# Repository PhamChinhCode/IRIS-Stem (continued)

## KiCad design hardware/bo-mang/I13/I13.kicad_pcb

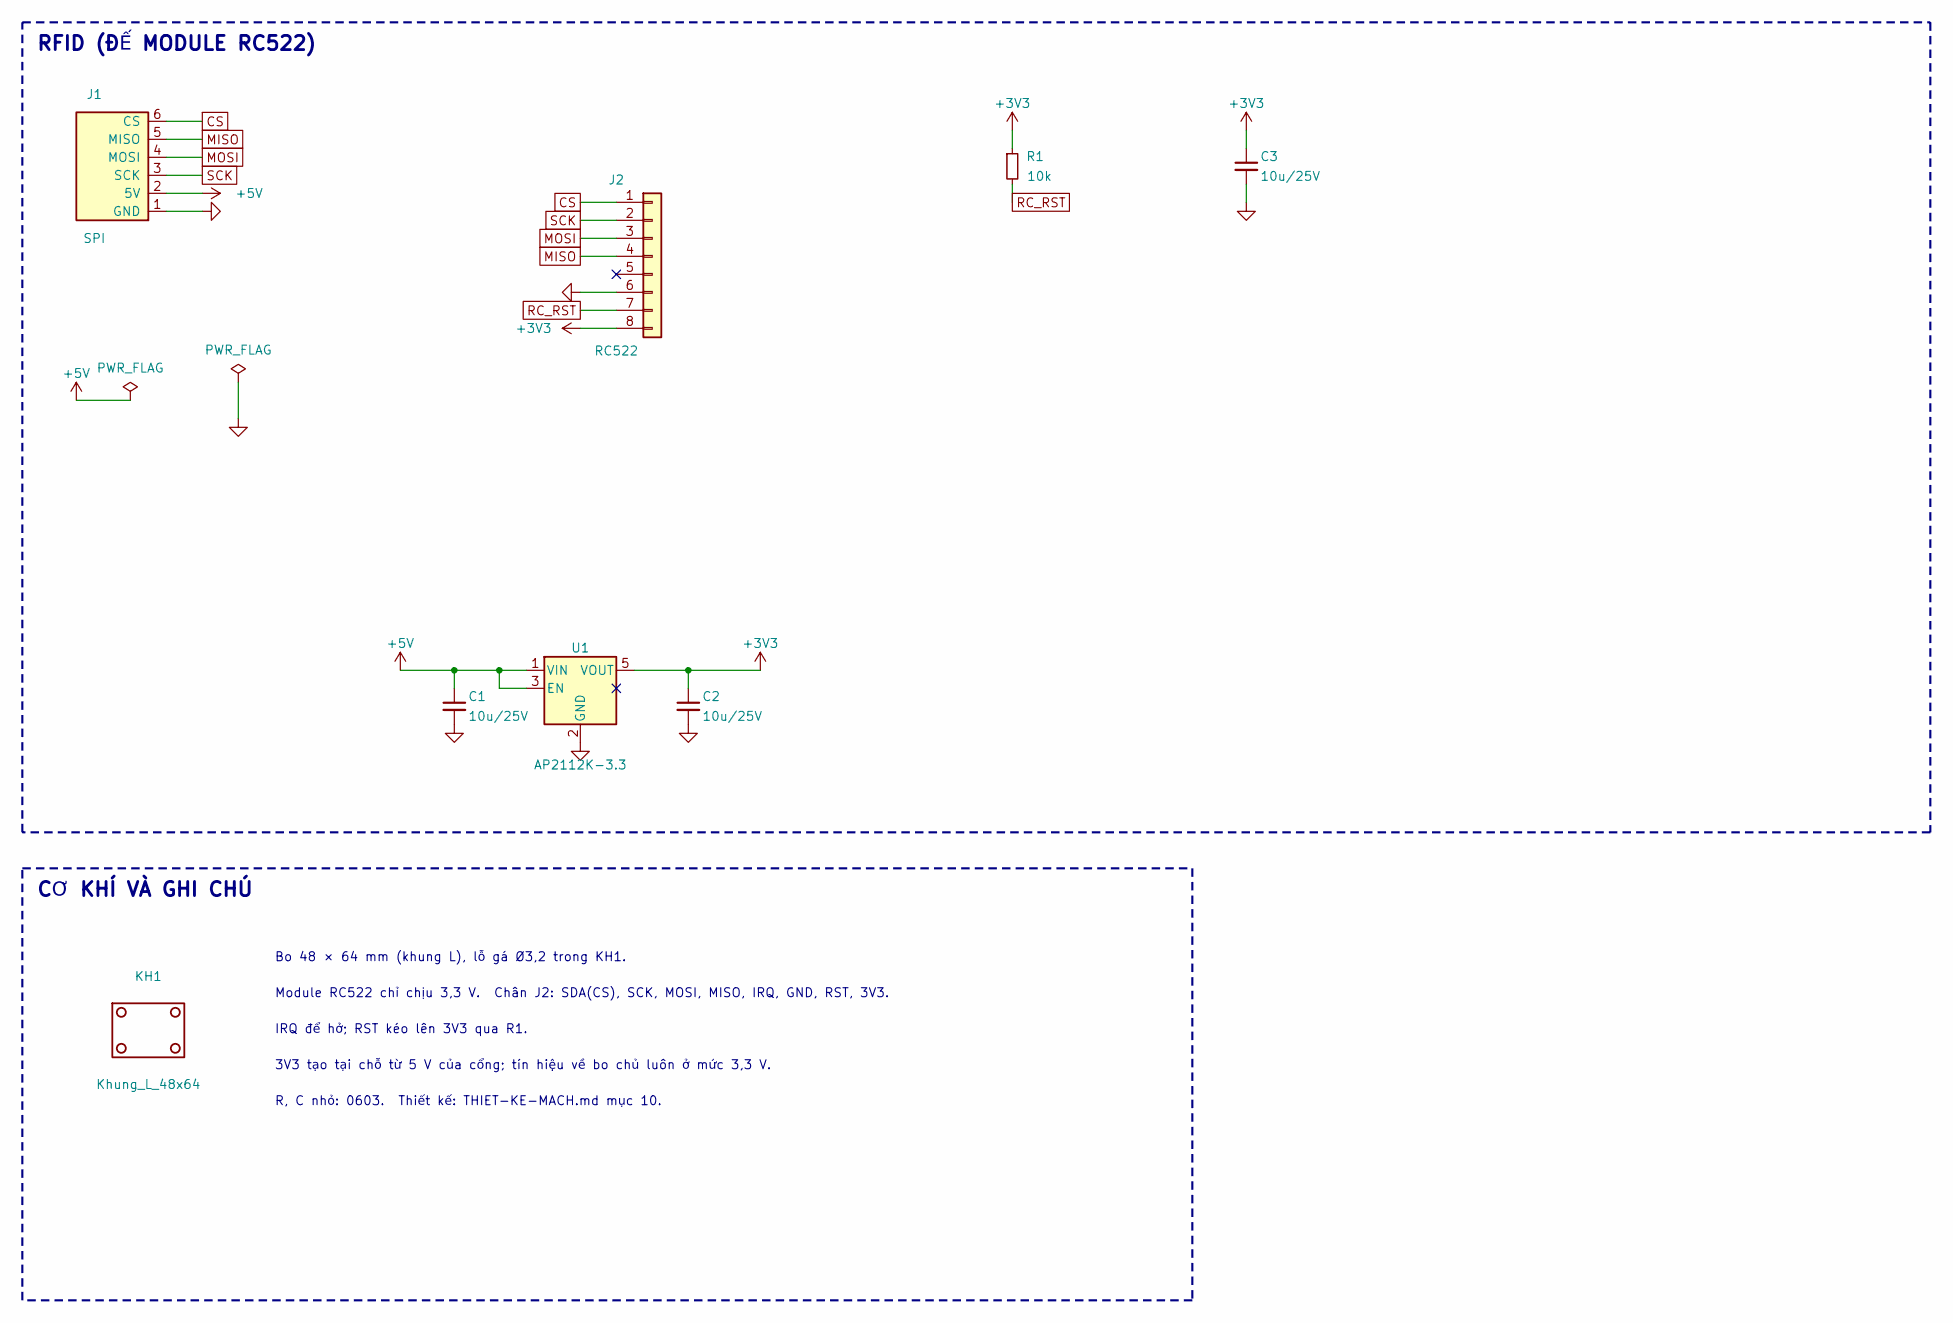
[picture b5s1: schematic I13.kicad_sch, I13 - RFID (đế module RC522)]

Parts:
C1, C2, C3: 10u/25V; C_0805_2012Metric
J1: SPI; Cong_PH_6P_Ngang
J2: RC522; PinSocket_1x08_P2.54mm_Vertical
KH1: Khung_L_48x64
R1: 10k; R_0603_1608Metric
U1: AP2112K-3.3; SOT-23-5; MPN AP2112K-3.3TRG1

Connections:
+3V3: C2.1, C3.1, J2.8, R1.1, U1.5 (VOUT)
+5V: C1.1, J1.2 (5V), U1.1 (VIN), U1.3 (EN)
CS: J1.6 (CS), J2.1
GND: C1.2, C2.2, C3.2, J1.1 (GND), J2.6, U1.2 (GND)
MISO: J1.5 (MISO), J2.4
MOSI: J1.4 (MOSI), J2.3
RC_RST: J2.7, R1.2
SCK: J1.3 (SCK), J2.2

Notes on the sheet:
RFID (ĐẾ MODULE RC522)
CƠ KHÍ VÀ GHI CHÚ
Bo 48 × 64 mm (khung L), lỗ gá Ø3,2 trong KH1.
Module RC522 chỉ chịu 3,3 V. Chân J2: SDA(CS), SCK, MOSI, MISO, IRQ, GND, RST, 3V3.
IRQ để hở; RST kéo lên 3V3 qua R1.
3V3 tạo tại chỗ từ 5 V của cổng; tín hiệu về bo chủ luôn ở mức 3,3 V.
R, C nhỏ: 0603. Thiết kế: THIET-KE-MACH.md mục 10.

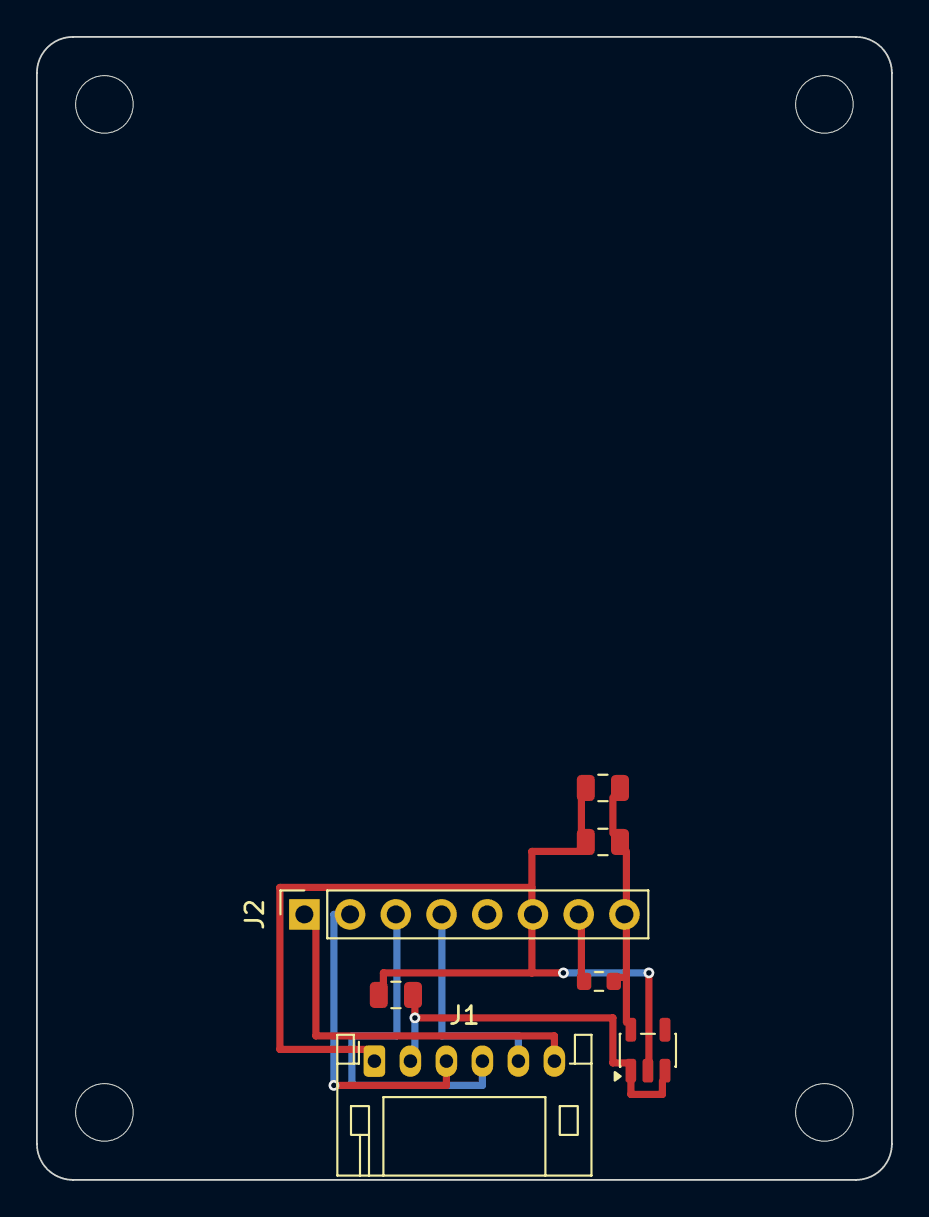
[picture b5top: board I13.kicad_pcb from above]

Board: 2 copper layers, 47.5 x 63.5 mm, 8 parts (0 on the bottom side), 8 nets.

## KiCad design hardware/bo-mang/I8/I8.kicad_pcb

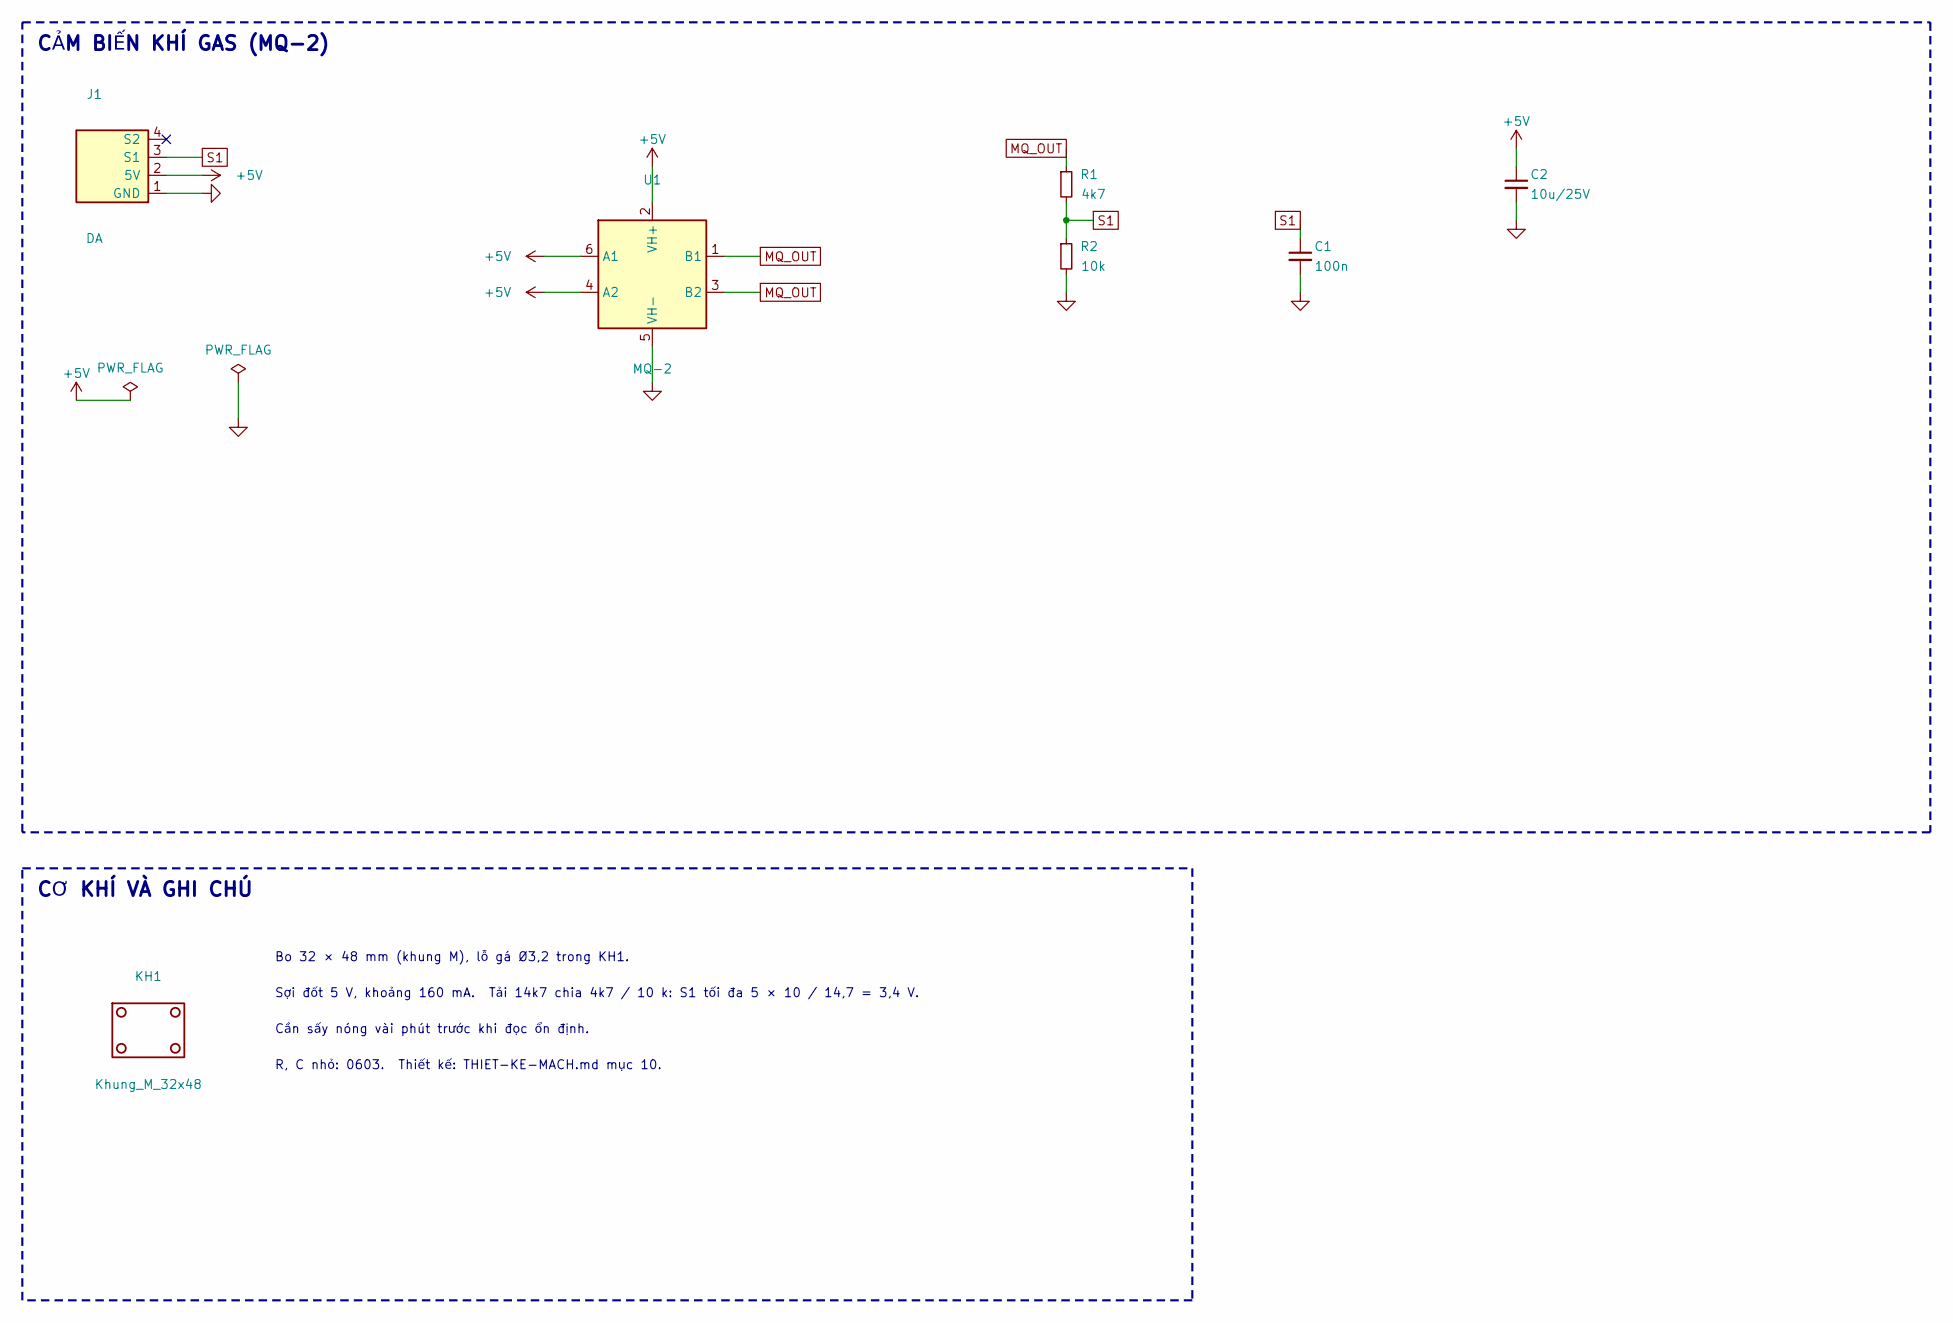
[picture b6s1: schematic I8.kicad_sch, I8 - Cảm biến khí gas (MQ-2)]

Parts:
C1: 100n; C_0603_1608Metric
C2: 10u/25V; C_0805_2012Metric
J1: DA; Cong_PH_4P_Ngang
KH1: Khung_M_32x48
R1: 4k7; R_0603_1608Metric
R2: 10k; R_0603_1608Metric
U1: MQ-2; MQ-6; MPN MQ-2

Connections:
+5V: C2.1, J1.2 (5V), U1.2 (VH+), U1.4 (A2), U1.6 (A1)
GND: C1.2, C2.2, J1.1 (GND), R2.2, U1.5 (VH-)
MQ_OUT: R1.1, U1.1 (B1), U1.3 (B2)
S1: C1.1, J1.3 (S1), R1.2, R2.1

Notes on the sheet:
CẢM BIẾN KHÍ GAS (MQ-2)
CƠ KHÍ VÀ GHI CHÚ
Bo 32 × 48 mm (khung M), lỗ gá Ø3,2 trong KH1.
Sợi đốt 5 V, khoảng 160 mA. Tải 14k7 chia 4k7 / 10 k: S1 tối đa 5 × 10 / 14,7 = 3,4 V.
Cần sấy nóng vài phút trước khi đọc ổn định.
R, C nhỏ: 0603. Thiết kế: THIET-KE-MACH.md mục 10.

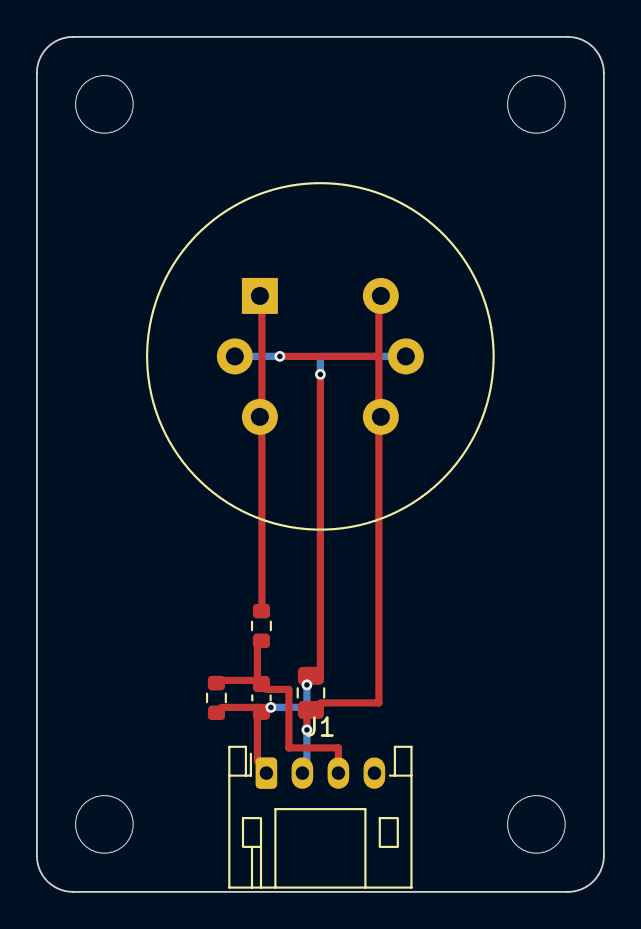
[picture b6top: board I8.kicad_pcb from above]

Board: 2 copper layers, 31.5 x 47.5 mm, 7 parts (0 on the bottom side), 4 nets.

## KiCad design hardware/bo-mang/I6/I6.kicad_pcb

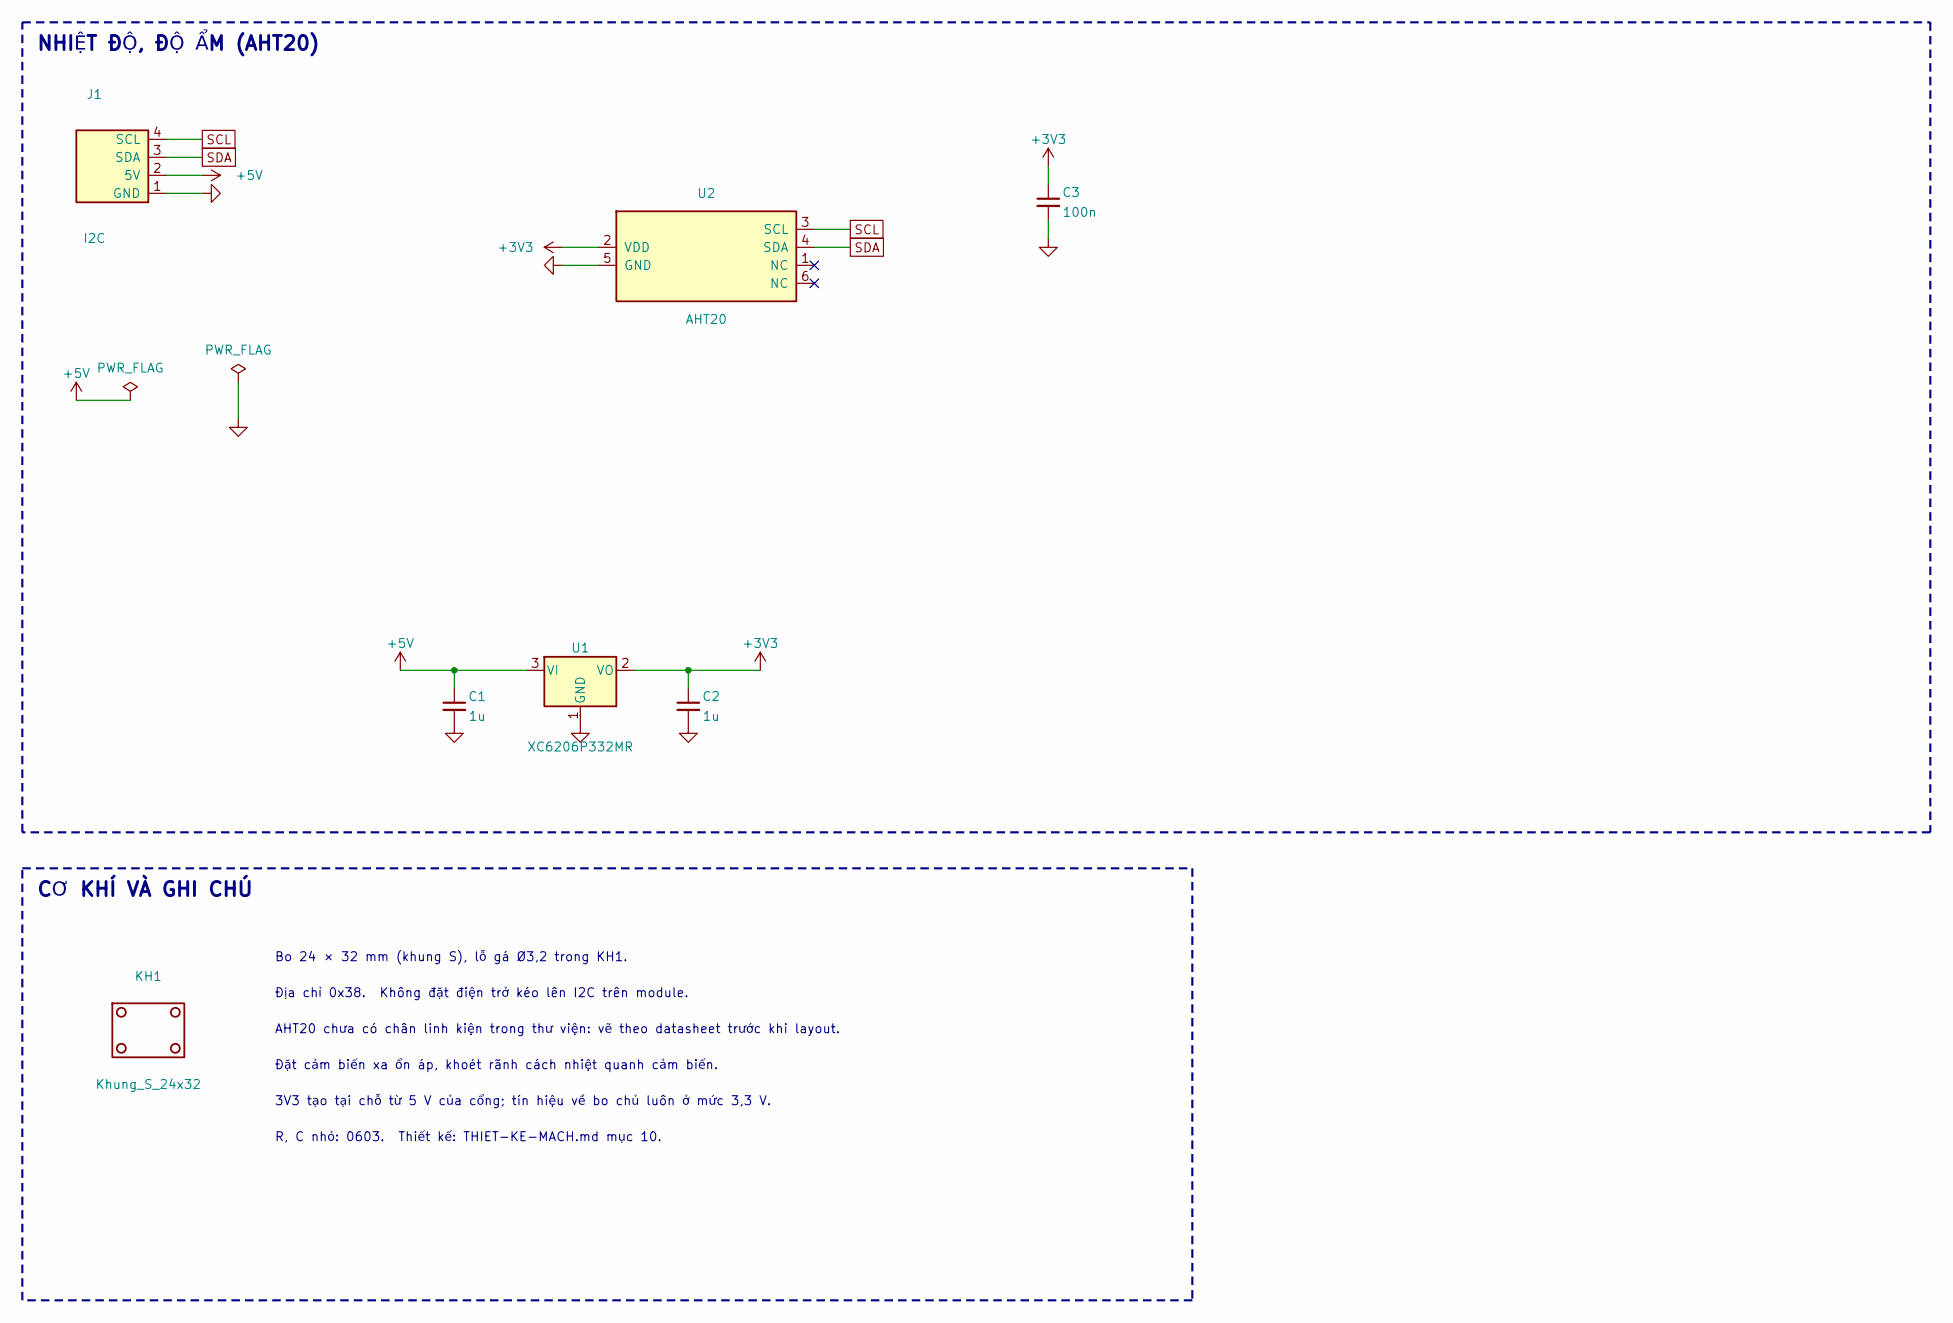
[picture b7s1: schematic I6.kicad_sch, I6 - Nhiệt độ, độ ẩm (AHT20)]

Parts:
C1, C2: 1u; C_0603_1608Metric
C3: 100n; C_0603_1608Metric
J1: I2C; Cong_PH_4P_Ngang
KH1: Khung_S_24x32
U1: XC6206P332MR; SOT-23-3; MPN XC6206P332MR
U2: AHT20; AHT20_DFN6_3x3; MPN AHT20

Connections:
+3V3: C2.1, C3.1, U1.2 (VO), U2.2 (VDD)
+5V: C1.1, J1.2 (5V), U1.3 (VI)
GND: C1.2, C2.2, C3.2, J1.1 (GND), U1.1 (GND), U2.5 (GND)
SCL: J1.4 (SCL), U2.3 (SCL)
SDA: J1.3 (SDA), U2.4 (SDA)

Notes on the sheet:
NHIỆT ĐỘ, ĐỘ ẨM (AHT20)
CƠ KHÍ VÀ GHI CHÚ
Bo 24 × 32 mm (khung S), lỗ gá Ø3,2 trong KH1.
Địa chỉ 0x38. Không đặt điện trở kéo lên I2C trên module.
AHT20 chưa có chân linh kiện trong thư viện: vẽ theo datasheet trước khi layout.
Đặt cảm biến xa ổn áp, khoét rãnh cách nhiệt quanh cảm biến.
3V3 tạo tại chỗ từ 5 V của cổng; tín hiệu về bo chủ luôn ở mức 3,3 V.
R, C nhỏ: 0603. Thiết kế: THIET-KE-MACH.md mục 10.

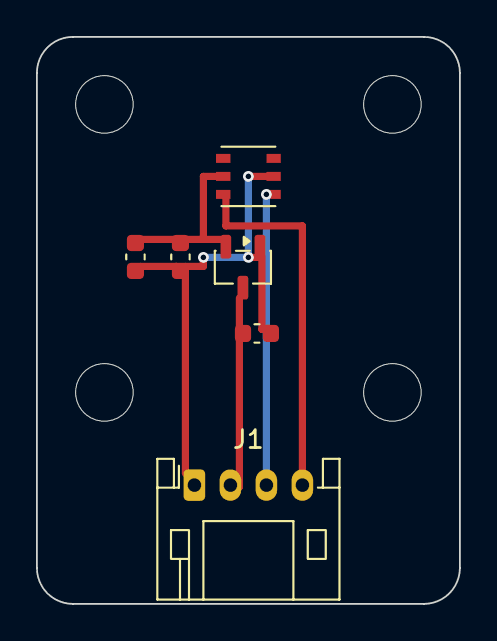
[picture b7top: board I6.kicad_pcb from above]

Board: 2 copper layers, 23.5 x 31.5 mm, 7 parts (0 on the bottom side), 5 nets.

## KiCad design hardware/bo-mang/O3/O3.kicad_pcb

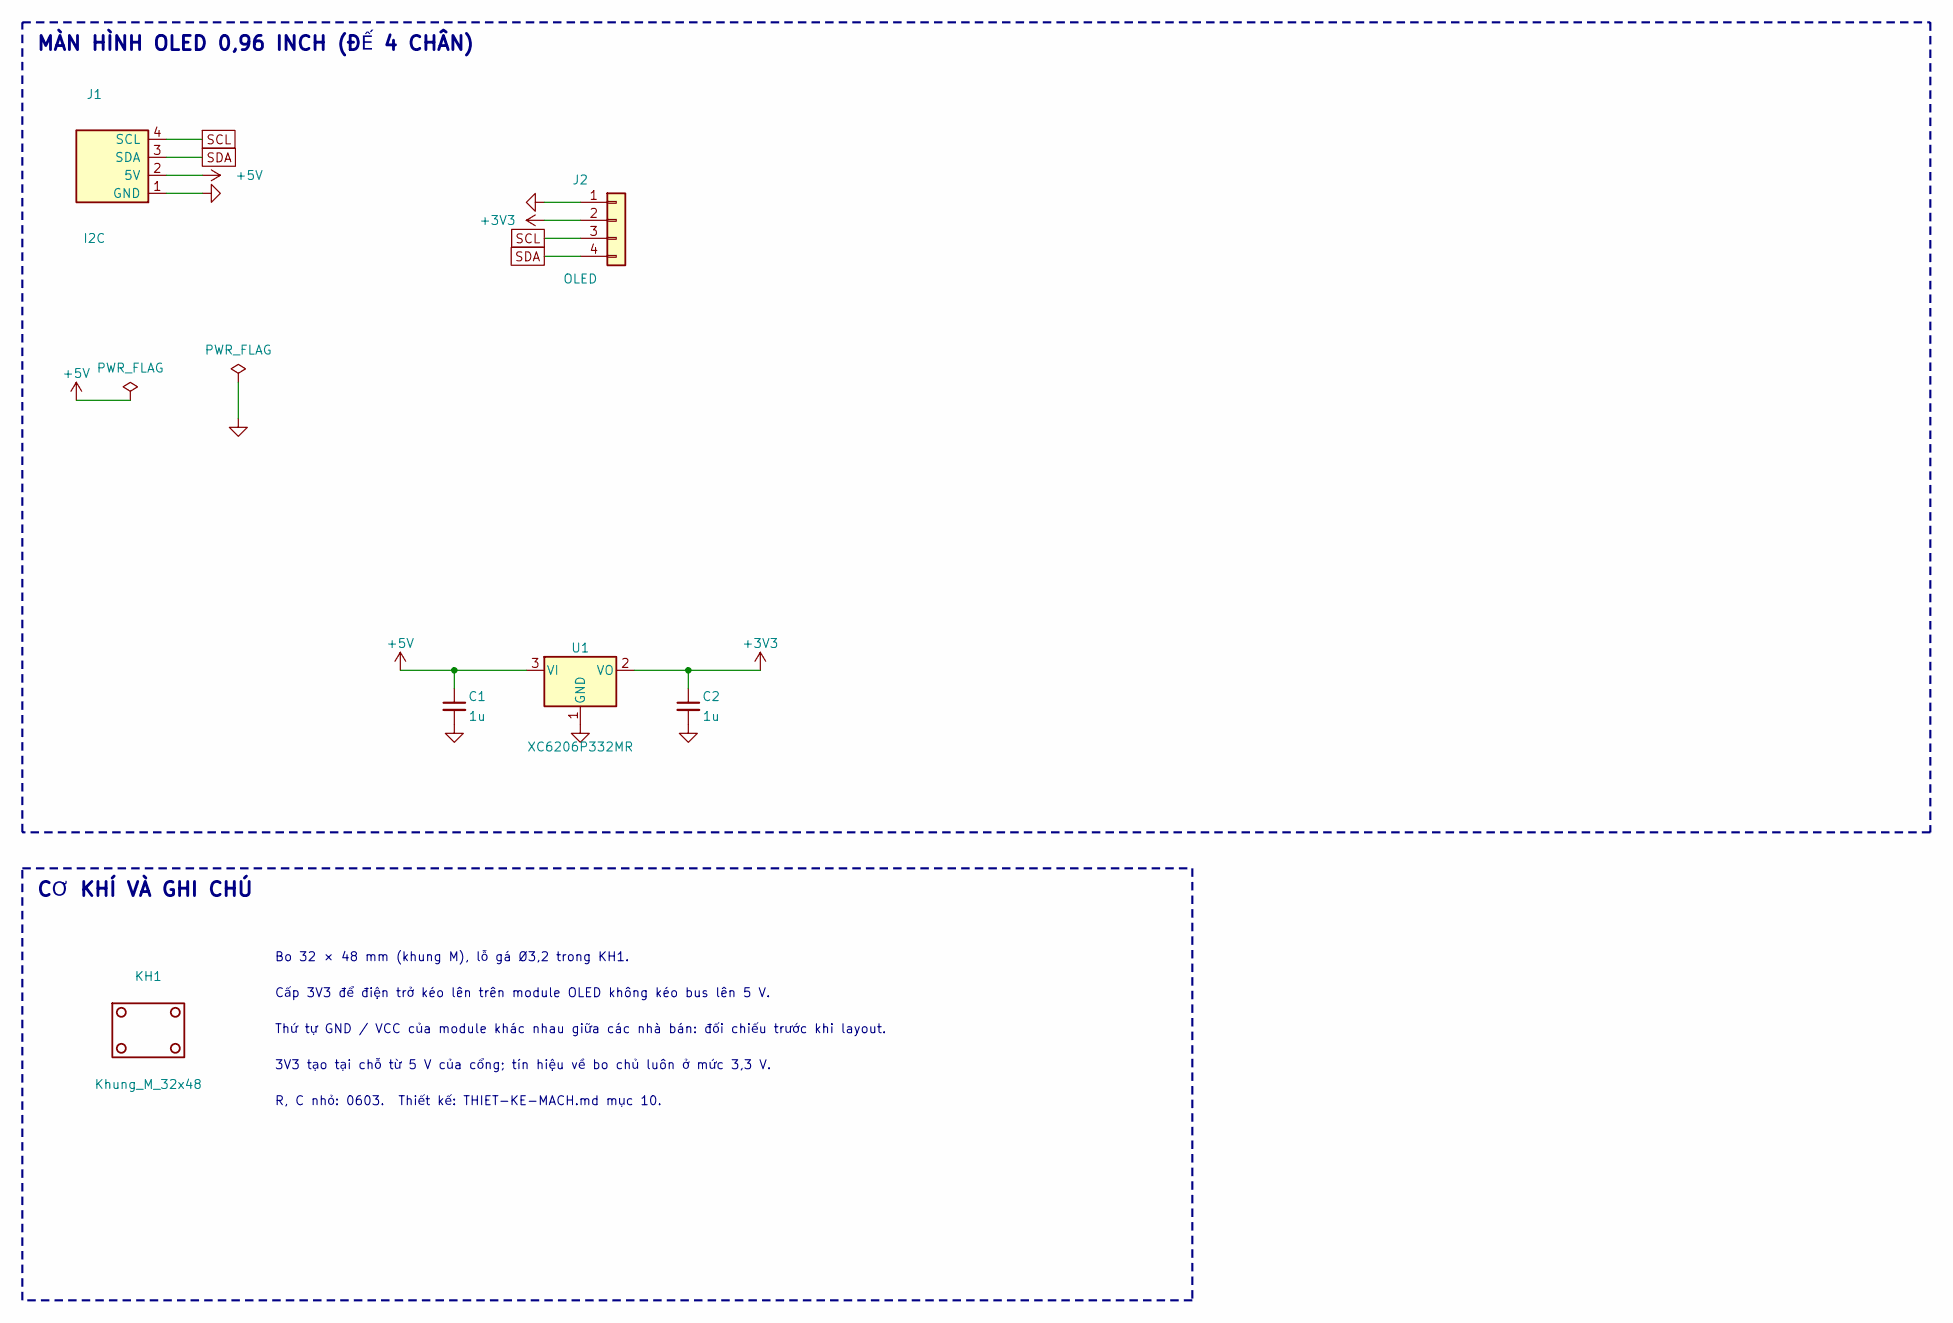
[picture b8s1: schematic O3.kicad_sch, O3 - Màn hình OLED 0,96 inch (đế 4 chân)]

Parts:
C1, C2: 1u; C_0603_1608Metric
J1: I2C; Cong_PH_4P_Ngang
J2: OLED; PinSocket_1x04_P2.54mm_Vertical
KH1: Khung_M_32x48
U1: XC6206P332MR; SOT-23-3; MPN XC6206P332MR

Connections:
+3V3: C2.1, J2.2, U1.2 (VO)
+5V: C1.1, J1.2 (5V), U1.3 (VI)
GND: C1.2, C2.2, J1.1 (GND), J2.1, U1.1 (GND)
SCL: J1.4 (SCL), J2.3
SDA: J1.3 (SDA), J2.4

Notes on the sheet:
MÀN HÌNH OLED 0,96 INCH (ĐẾ 4 CHÂN)
CƠ KHÍ VÀ GHI CHÚ
Bo 32 × 48 mm (khung M), lỗ gá Ø3,2 trong KH1.
Cấp 3V3 để điện trở kéo lên trên module OLED không kéo bus lên 5 V.
Thứ tự GND / VCC của module khác nhau giữa các nhà bán: đối chiếu trước khi layout.
3V3 tạo tại chỗ từ 5 V của cổng; tín hiệu về bo chủ luôn ở mức 3,3 V.
R, C nhỏ: 0603. Thiết kế: THIET-KE-MACH.md mục 10.

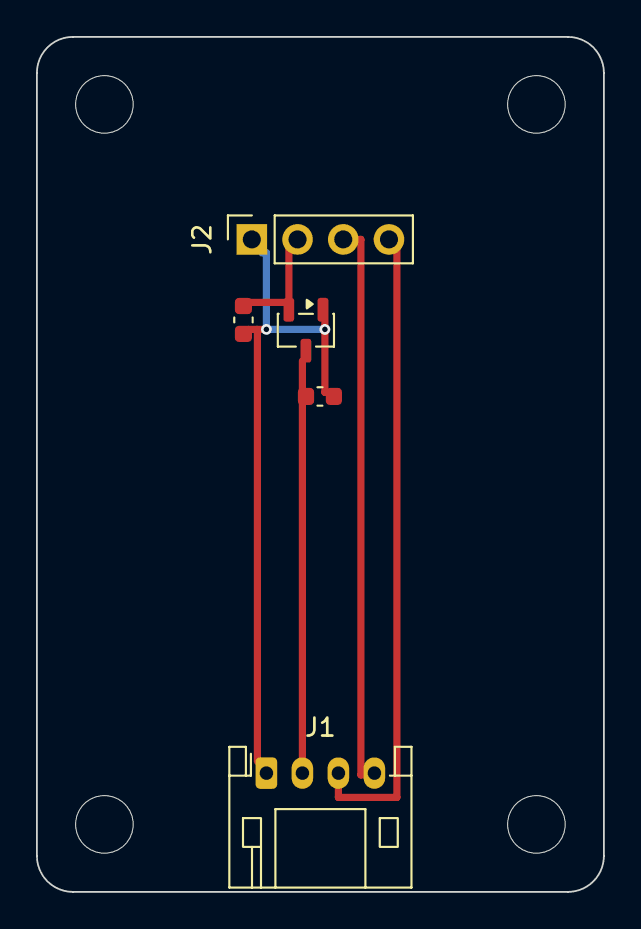
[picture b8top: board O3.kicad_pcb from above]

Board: 2 copper layers, 31.5 x 47.5 mm, 6 parts (0 on the bottom side), 5 nets.
